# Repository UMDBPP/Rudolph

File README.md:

# Rudolph
2nd version of a LoRa tracker now using a +30dBm radio coupled with a MIA-M10 for proper tracking.

The system is split into two boards. The primary "logic" board contains the embedded and RF devices. The PowerPack contains all of the necessary circuitry to switch between USB and Battery power sources as well as produce +5V and +3.3V filtered supply rails.

# Bill Of Materials (BOM)
Digi-Key BOM for this project: [https://www.digikey.com/en/mylists/list/V9B8HP1SN9](https://www.digikey.com/en/mylists/list/V9B8HP1SN9)

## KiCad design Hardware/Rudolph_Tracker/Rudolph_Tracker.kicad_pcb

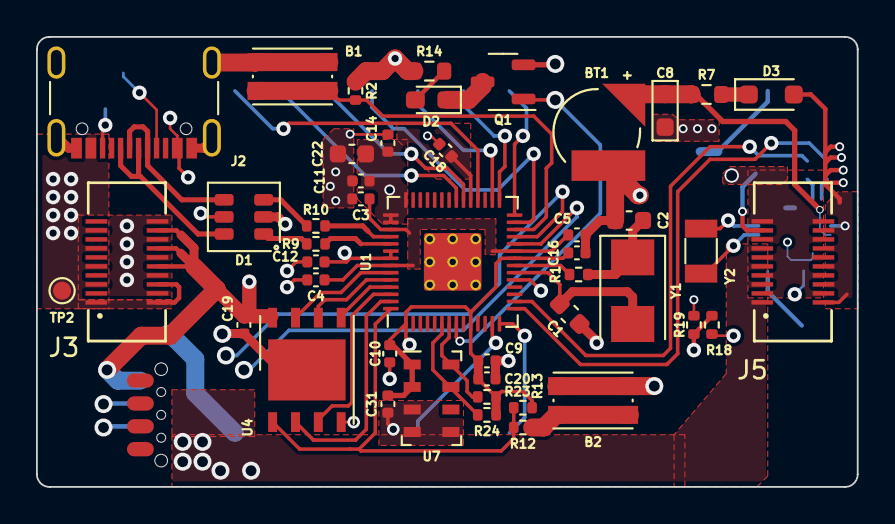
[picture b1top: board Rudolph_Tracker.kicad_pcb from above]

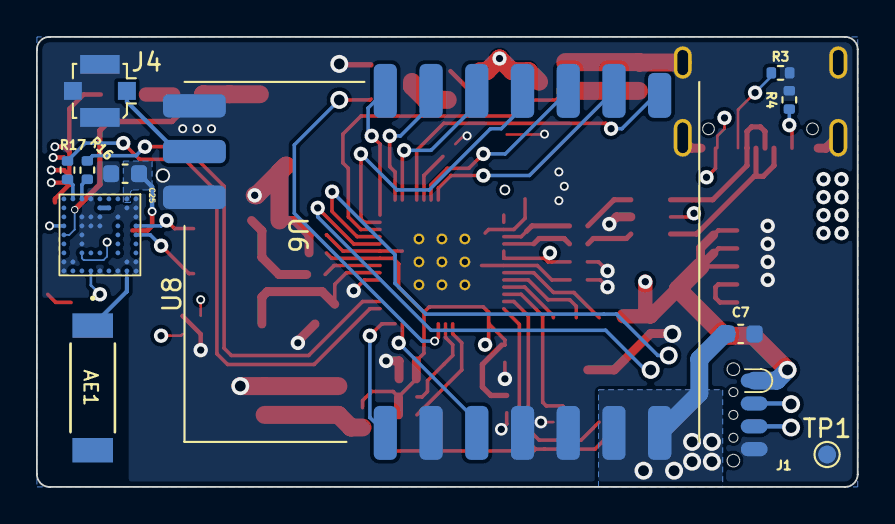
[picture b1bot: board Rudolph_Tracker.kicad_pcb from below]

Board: 4 copper layers, 45.6 x 25.0 mm, 57 parts (12 on the bottom side), 52 nets.

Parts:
AE1: Antenna; ANT_1575AT_JOT-M
B1, B2: KMR2; SW_Push_1P1T_NO_CK_KMR2
BT1: ML414H IV01E; SEIKO_ML414H_IV01E
C1, C2: 22pF; C_0603_1608Metric
C3, C4, C10, C11, C12, C14, C16, C18, C19, C20, C31: 100nF; C_0402_1005Metric
C5, C9: 1uF; C_0402_1005Metric
C7, C22: 10uF; C_0603_1608Metric
C8: 1uF; R_0603_1608Metric_Pad0.98x0.95mm_HandSolder
C25: 100nF; C_0603_1608Metric
D1: USBLC6-2SC6; SOT-23-6
D2: LED; D_0603_1608Metric_Pad1.05x0.95mm_HandSolder
D3: NSR0530HT1G; D_SOD-323_HandSoldering
J1: SOICbite; SOIC_clipProgSmall
J2: USB_C_Receptacle_USB2.0; USB_C_Receptacle_GCT_USB4105-xx-A_16P_TopMnt_Horizontal
J3, J5: 537480208; CON_537480208
J4: U.FL; U.FL_Molex_MCRF_73412-0110_Vertical
Q1: IRLML0060TRPBF; SOT-23-3
R1, R12: 1k; R_0402_1005Metric
R2, R13, R23, R24: 10k; R_0402_1005Metric
R3, R4: 5.1k; R_0402_1005Metric
R7: 1k; R_0603_1608Metric
R9, R10: 27; R_0402_1005Metric
R14: 590; R_0603_1608Metric
R16, R17: 33; R_0402_1005Metric
R18, R19: 0; R_0402_1005Metric
TP1, TP2: TestPoint; TestPoint_Pad_D1.0mm
U1: RP2040; RP2040-QFN-56
U4: W25Q128JVS; W25Q64JVZP
U6: MIA-M10Q
U7: MS5607-02BA; LGA-8_3x5mm_P1.25mm
U8: DRF1262TL
Y1: 445I23D12M00000; Crystal_SMD_5032-2Pin_5.0x3.2mm
Y2: 32.768k; Crystal_SMD_3215-2Pin_3.2x1.5mm

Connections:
+1V1: C3.1, C4.1, C5.1, U1.23 (DVDD), U1.45 (VREG_VOUT), U1.50 (DVDD)
+3V3: C9.1, C10.1, C11.1, C12.1, C14.1, C16.1, C18.1, C19.1, C20.1, C22.1, C25.1, C31.1, D3.2 (A), J1.1, J3.15, J3.17, J3.19, J5.9, J5.11, J5.13, J5.15, J5.17, J5.19, R2.1, R13.1, R14.1, R23.1, R24.1, U1.1 (IOVDD), U1.10 (IOVDD), U1.22 (IOVDD), U1.33 (IOVDD), U1.42 (IOVDD), U1.43 (ADC_AVDD), U1.44 (VREG_IN), U1.48 (USB_VDD), U1.49 (IOVDD), U4.8 (VCC), U6.B1 (VCC), U6.J4 (V_IO), U7.1 (VDD), U7.2 (PS)
+5V: C7.1, J5.1, J5.3, J5.5, J5.7, U8.6 (VDD), U8.7 (VDD)
/BUSY: U1.35 (GPIO23), U8.9 (BUSY)
/D1: Q1.1 (G), U1.8 (GPIO6)
/DIO1: U1.32 (GPIO21), U8.8 (DIO1)
/GPS_RX: R17.1, U1.15 (GPIO12)
/GPS_TX: R16.1, U1.16 (GPIO13)
/QSPI_SCLK: U1.52 (QSPI_SCLK), U4.6 (CLK)
/QSPI_SD0: U1.53 (QSPI_SD0), U4.5 (DI(IO0))
/QSPI_SD1: U1.55 (QSPI_SD1), U4.2 (DO(IO1))
/QSPI_SD2: U1.54 (QSPI_SD2), U4.3 (IO2)
/QSPI_SD3: U1.51 (QSPI_SD3), U4.7 (IO3)
/QSPI_SS: R12.2, R13.2, U1.56 (QSPI_SS), U4.1 (~CS)
/SCL: R23.2, U1.7 (GPIO5), U7.8 (SCLK)
/SDA: R24.2, U1.6 (GPIO4), U7.7 (SDI/SDA)
/SPI0_CS: U1.28 (GPIO17), U8.14 (NSS)
/SPI0_MISO: U1.27 (GPIO16), U8.11 (MISO)
/SPI0_MOSI: U1.30 (GPIO19), U8.12 (MOSI)
/SPI0_SCK: U1.29 (GPIO18), U8.13 (SCK)
/SW: U1.14 (GPIO11), U8.1 (SW)
/SWCLK: J1.3, U1.24 (SWCLK)
/SWD: J1.2, U1.25 (SWD)
/TXEN: U1.13 (GPIO10), U8.3 (TXEN)
/USB_D+: D1.1 (L1), R9.2
/USB_D-: D1.3 (L2), R10.2
/V_BCKP: BT1.1 (+), C8.1, R7.2, U6.J5 (V_BCKP)
/~RST: U1.34 (GPIO22), U8.10 (RST)
GND: B1.1, B2.1, BT1.2 (-), C1.1, C2.1, C3.2, C4.2, C5.2, C7.2, C8.2, C9.2, C10.2, C11.2, C12.2, C14.2, C16.2, C18.2, C19.2, C20.2, C22.2, C25.2, C31.2, D1.2 (VN), J1.4, J2.A1 (GND), J2.A12 (GND), J2.B1 (GND), J2.B12 (GND), J2.S1 (SHIELD), J3.2, J3.4, J3.6, J3.8, J3.10, J3.12, J3.14, J3.16, J3.18, J3.20, J4.2 (Ext), J5.2, J5.4, J5.6, J5.8, J5.10, J5.12, J5.14, J5.16, J5.18, J5.20, Q1.2 (S), R3.2, R4.2, R18.2, R19.2, TP1.1, U1.19 (TESTEN), U1.57 (GND), U4.4 (GND), U4.9 (EP), U6.A1 (GND), U6.A2 (GND), U6.A3 (GND), U6.A8 (GND), U6.A9 (GND), U6.B2 (GND), U6.B8 (GND), U6.C3 (GND), U6.C9 (GND), U6.E3 (GND), U6.E4 (GND), U6.E9 (GND), U6.F1 (GND), U6.F3 (GND), U6.F4 (GND), U6.G3 (GND), U6.G4 (GND), U6.G5 (GND), U6.G6 (GND), U6.H8 (GND), U6.J8 (GND), U6.J9 (GND), U7.3 (GND), U7.4 (CSB), U7.5 (CSB), U8.2 (GND), U8.4 (GND), U8.5 (GND), U8.15 (GND), U8.17 (GND)
unnamed: AE1.1 (A), U6.B9 (RF_IN)
unnamed: B2.2, R12.1
unnamed: C2.2, R1.1, Y1.1
unnamed: D1.6 (L1), J2.A6 (D+), J2.B6 (D+)
unnamed: D1.4 (L2), J2.A7 (D-), J2.B7 (D-)
unnamed: D2.2 (A), R14.2
unnamed: D2.1 (K), Q1.3 (D)
unnamed: D3.1 (K), R7.1
unnamed: J2.A5 (CC1), R3.1
unnamed: J2.B5 (CC2), R4.1
unnamed: J4.1 (In), U8.16 (ANT)
unnamed: R18.1, U6.F9 (RSRVD)
unnamed: R19.1, U6.G7 (RSRVD)
unnamed: B1.2, R2.2, U1.26 (RUN)
unnamed: R10.1, U1.46 (USB_DM)
unnamed: R9.1, U1.47 (USB_DP)
unnamed: C1.2, U1.20 (XIN), Y1.2
unnamed: R1.2, U1.21 (XOUT)
unnamed: U6.A4 (RTC_I), Y2.2
unnamed: U6.A5 (RTC_O), Y2.1
unnamed: R17.2, U6.H1 (RX)
unnamed: R16.2, U6.G1 (TX)
VBUS: D1.5 (VP), J2.A4 (VBUS), J2.A9 (VBUS), J2.B4 (VBUS), J2.B9 (VBUS), J3.1, J3.3, J3.5, J3.7, J3.9, J3.11, J3.13, TP2.1

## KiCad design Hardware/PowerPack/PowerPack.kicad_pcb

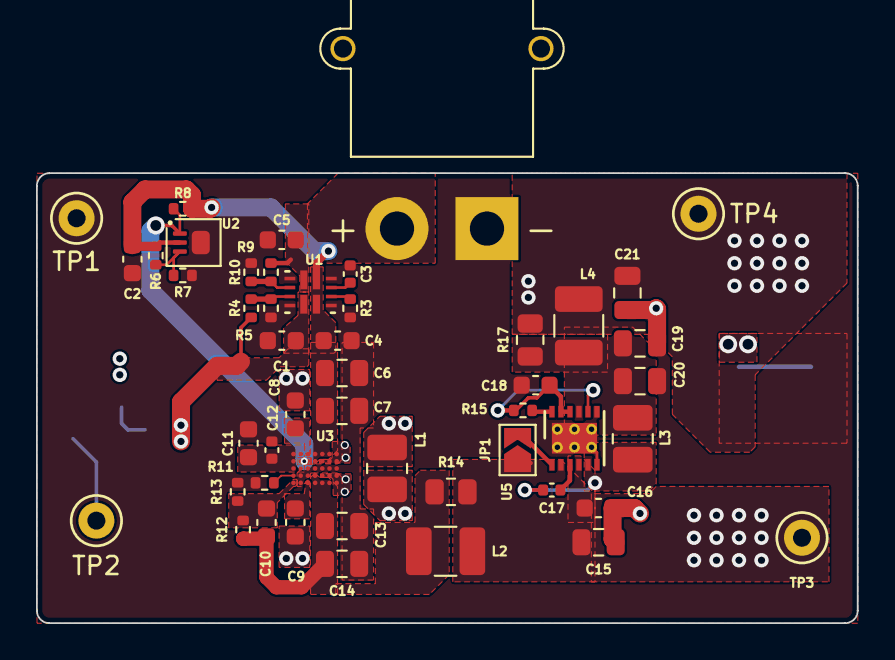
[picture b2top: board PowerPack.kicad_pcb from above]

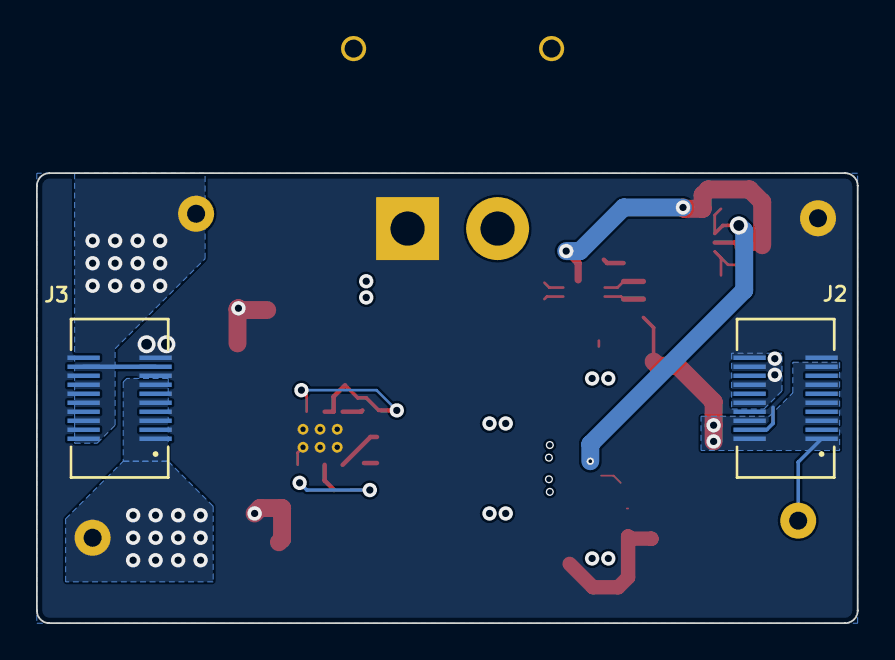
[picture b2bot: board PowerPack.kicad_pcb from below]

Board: 4 copper layers, 45.6 x 25.0 mm, 51 parts (2 on the bottom side), 26 nets.

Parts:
C1, C5: 10uF; C_0603_1608Metric
C2, C4, C18: 1uF; C_0603_1608Metric
C3: 10nF; C_0402_1005Metric
C6, C7, C13, C14: 10uF; C_0805_2012Metric
C8, C9: 220nF; C_0603_1608Metric
C10: 10pF; C_0603_1608Metric
C11: 2.2uF; C_0603_1608Metric
C12: 470nF; C_0402_1005Metric
C15, C19, C20, C21: 15uF; C_0805_2012Metric
C16: 4.7uF; C_0603_1608Metric
C17: 0.1uF; C_0402_1005Metric
J2, J3: 529910208; CON_529910208
J4: XT30; AMASS_XT30PW-M_1x02_P2.50mm_Horizontal
JP1: SolderJumper_2_Open; SolderJumper-2_P1.3mm_Open_TrianglePad1.0x1.5mm
L1: 1.0uH; L_1008_2520Metric_Pad1.43x2.20mm_HandSolder
L2, L4: 3.3uH; L_1210_3225Metric_Pad1.42x2.65mm_HandSolder
L3: 2.2uH; L_1008_2520Metric_Pad1.43x2.20mm_HandSolder
R3: 44.2k; R_0402_1005Metric
R4, R9: 23.7k; R_0402_1005Metric
R5, R10: 5k; R_0402_1005Metric
R6: 1.05M; R_0402_1005Metric
R7: 154k; R_0402_1005Metric
R8: 510k; R_0402_1005Metric
R11: 64.9k; R_0402_1005Metric
R12: 178k; R_0402_1005Metric
R13: 12.7k; R_0402_1005Metric
R14, R17: 100m; R_0805_2012Metric
R15: 20k; R_0402_1005Metric
TP1, TP2, TP3, TP4: TestPoint; TestPoint_Keystone_5000-5004_Miniature
U1: TPS2121RUXR; TPS2121
U2: LT6703CDC-3; DFN-3-1EP-2x2mm_P0.5mm_EP1x1.35mm
U3: MAX77857; MAX77857-35WLP
U5: MAX25232ATCB/V+T; MAX25232

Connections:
+3V3: C21.1, J2.15, J2.17, J2.19, J3.9, J3.11, J3.13, J3.15, J3.17, J3.19, L4.2, R17.2, TP4.1
+5V: C15.1, C16.1, J3.1, J3.3, J3.5, J3.7, JP1.1 (A), L2.2, R14.2, TP3.1, U5.2 (EN), U5.4 (SUP)
+BATT: C5.1, J4.2, R9.1, U1.2 (IN2)
+VDC: C2.1, C4.1, C6.1, C7.1, R6.1, R8.1, U1.1 (OUT), U1.8 (OUT), U2.2 (V+), U3.A4 (IN), U3.A5 (IN), U3.A6 (IN), U3.B4 (IN)
/LVC: R8.2, U2.1 (OUT), U3.B2 (EN), U3.B3 (EN)
GND: C1.2, C2.2, C3.2, C4.2, C5.2, C6.2, C7.2, C11.2, C12.2, C13.2, C14.2, C15.2, C16.2, C18.2, C19.2, C20.2, C21.2, J2.2, J2.4, J2.6, J2.8, J2.10, J2.12, J2.14, J2.16, J2.18, J2.20, J3.2, J3.4, J3.6, J3.8, J3.10, J3.12, J3.14, J3.16, J3.18, J3.20, J4.1, R3.2, R5.2, R7.2, R10.2, R11.1, R13.2, TP1.1, U1.3 (CP2), U1.6 (PR1), U1.9 (ST), U1.12 (GND), U2.4 (V-), U3.C3 (PGND), U3.C4 (PGND), U3.C5 (PGND), U3.C6 (PGND), U3.C7 (PGND), U3.D2 (PGND), U3.D3 (PGND), U3.E2 (AGND), U5.6 (PGND), U5.7 (AGND), U5.EP (GND)
unnamed: C8.2, L1.1, U3.A7 (LX1), U3.B5 (LX1), U3.B6 (LX1), U3.B7 (LX1)
unnamed: C9.1, L1.2, U3.D5 (LX2), U3.D6 (LX2), U3.D7 (LX2), U3.E7 (LX2)
unnamed: C10.1, C13.1, C14.1, L2.1, R12.1, R14.1, U3.D4 (OUT), U3.E4 (OUT), U3.E5 (OUT), U3.E6 (OUT)
unnamed: JP1.2 (B), U5.1 (SPS)
unnamed: R3.1, U1.10 (ILM)
unnamed: R4.2, R5.1, U1.5 (OV1)
unnamed: R9.2, R10.1, U1.4 (OV2)
unnamed: C3.1, U1.11 (SS)
unnamed: R6.2, R7.1, U2.3 (IN+)
unnamed: C8.1, U3.A3 (BST1)
unnamed: C9.2, U3.E3 (BST2)
unnamed: C10.2, R12.2, R13.1, U3.E1 (FB)
unnamed: C11.1, C12.1, U3.A1 (SCL), U3.A2 (VIO), U3.B1 (SDA), U3.C1 (VL)
unnamed: R11.2, U3.D1 (SEL)
unnamed: C18.1, R15.2, U5.8 (FB), U5.10 (BIAS), U5.11 (SYNC)
unnamed: C17.1, U5.3 (BST)
unnamed: C17.2, L3.1, U5.5 (LX)
unnamed: C19.1, C20.1, L3.2, L4.1, R17.1, U5.9 (OUT)
unnamed: R15.1, U5.12 (PGOOD)
VBUS: C1.1, J2.1, J2.3, J2.5, J2.7, J2.9, J2.11, J2.13, R4.1, TP2.1, U1.7 (IN1)

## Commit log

2023-09-26 init with first routing pass
2023-09-26 banishing DS_Store
2023-09-26 flipped some connectors
2023-09-26 generating gerbers
2023-09-28 generating some BOMs
2023-11-03 messing with libraries
2023-11-03 more library shenanigans
